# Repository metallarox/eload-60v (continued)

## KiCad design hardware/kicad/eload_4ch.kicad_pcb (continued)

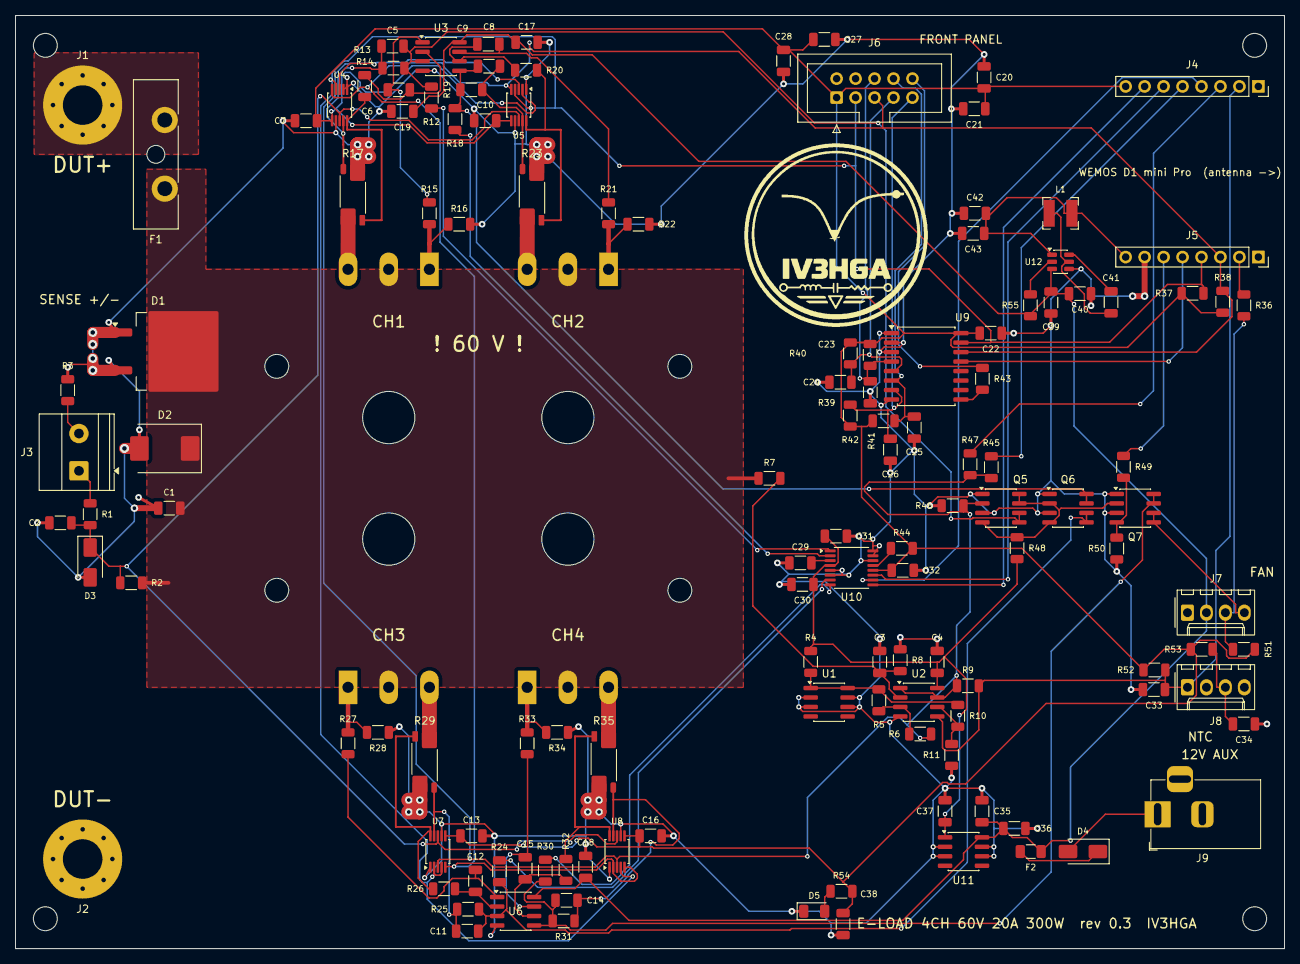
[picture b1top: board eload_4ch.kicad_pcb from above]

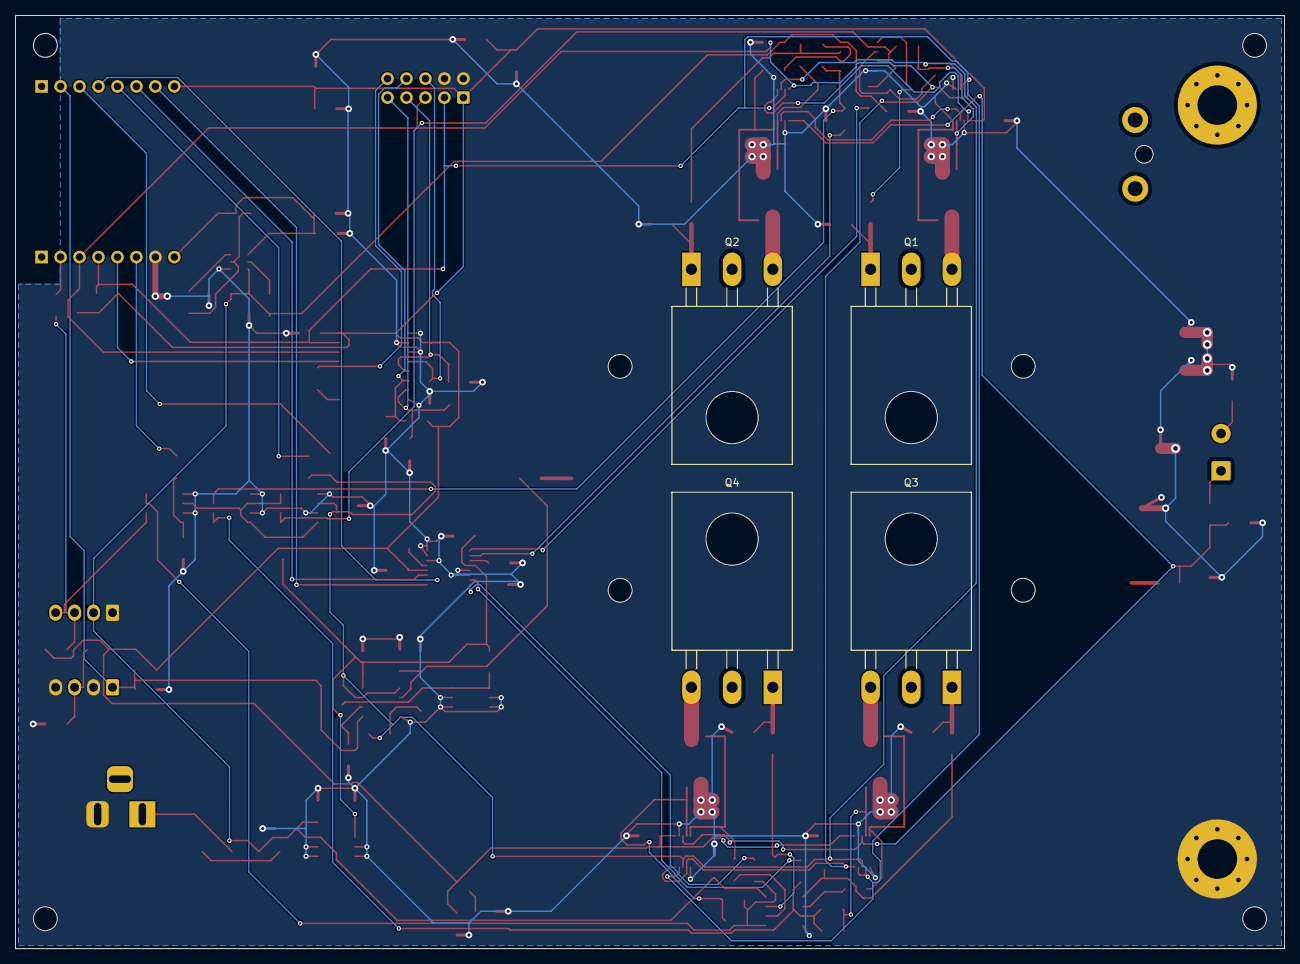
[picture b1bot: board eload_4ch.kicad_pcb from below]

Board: 2 copper layers, 170.0 x 125.0 mm, 143 parts (4 on the bottom side), 77 nets.

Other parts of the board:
H1, H2, H3, H4: M3; MountingHole_3.2mm_M3
H5, H6, H7, H8: M3 nylon (spreader); MountingHole_3.2mm_M3
LOGO1: Logo_IV3HGA; Logo_IV3HGA_25mm

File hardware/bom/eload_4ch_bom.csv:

"Reference","Qty","Value","Footprint","MPN","Note"
"C1","1","100n 100V","Capacitor_SMD:C_1206_3216Metric","","X7R"
"C2","1","10n 100V","Capacitor_SMD:C_1206_3216Metric","",""
"C3,C4,C7,C10,C13,C16,C20,C22,C28-C30,C32-C34,C36","15","100n","Capacitor_SMD:C_1206_3216Metric","",""
"C5,C8,C11,C14","4","10n C0G","Capacitor_SMD:C_1206_3216Metric","","Setpoint filter 16.6 kHz (rev 0.2)"
"C6,C9,C12,C15","4","1n C0G","Capacitor_SMD:C_1206_3216Metric","","Loop compensation rev 0.2: PM ~80 deg, BW 6-15 kHz"
"C17,C18,C40,C41","4","100n 50V","Capacitor_SMD:C_1206_3216Metric","",""
"C19,C21,C27,C35,C38,C39","6","10u 25V","Capacitor_SMD:C_1206_3216Metric","","OLED decoupling"
"C23-C26","4","10n","Capacitor_SMD:C_1206_3216Metric","","Debounce 100 us"
"C31,C37","2","1u","Capacitor_SMD:C_1206_3216Metric","",""
"C42,C43","2","22u 10V","Capacitor_SMD:C_1206_3216Metric","",""
"D1","1","VS-30CTQ100S","Package_TO_SOT_SMD:TO-263-2","VS-30CTQ100SPbF","Reverse polarity: conducts and blows F1 (check I2t)"
"D2","1","SMCJ64CA","Diode_SMD:D_SMC","SMCJ64CA",""
"D3","1","SMAJ64CA","Diode_SMD:D_SMA","SMAJ64CA",""
"D4","1","SS34","Diode_SMD:D_SMA","SS34",""
"D5","1","green","LED_SMD:LED_1206_3216Metric","",""
"F1","1","25A ATO","Fuse:Fuseholder_Blade_ATO_Littelfuse_Pudenz_2_Pin","","ATO blade fuse 25 A"
"F2","1","1.5A","Fuse:Fuse_1206_3216Metric","","PTC 1206, 1.5 A hold (WiFi buck + fan)"
"J1","1","DUT+","MountingHole:MountingHole_5.3mm_M5_Pad_Via","","M5 stud, 25 A"
"J2","1","DUT-","MountingHole:MountingHole_5.3mm_M5_Pad_Via","","M5 stud, 25 A - ground star point"
"J3","1","SENSE","TerminalBlock_Phoenix:TerminalBlock_Phoenix_MKDS-1,5-2_1x02_P5.00mm_Horizontal","","1=SENSE+ 2=SENSE-"
"J4","1","D1mini L","Connector_PinSocket_2.54mm:PinSocket_1x08_P2.54mm_Vertical","","RST A0 D0(GPIO16) D5(14) D6(12) D7(13) D8(15) 3V3; the module 3V3 powers the logic"
"J5","1","D1mini R","Connector_PinSocket_2.54mm:PinSocket_1x08_P2.54mm_Vertical","","TX RX(GPIO3) D1(5) D2(4) D3(0)=expander INT D4(2) G 5V; GPIO0/2/15 = strapping"
"J6","1","FRONT PANEL","Connector_IDC:IDC-Header_2x05_P2.54mm_Vertical","","10-wire ribbon to the front panel: OLED SSD1309/SH1106 0x3C, EC11 encoder, OUTPUT button"
"J7","1","FAN","Connector_Molex:Molex_KK-254_AE-6410-04A_1x04_P2.54mm_Vertical","","12 V 4-wire fan (SP3/TR4 cooler)"
"J8","1","NTC","Connector_Molex:Molex_KK-254_AE-6410-04A_1x04_P2.54mm_Vertical","","2x NTC 10k B3950 glued to the spreader"
"J9","1","12V DC","Connector_BarrelJack:BarrelJack_Horizontal","",""
"L1","1","6u8","Inductor_SMD:L_Bourns-SRN4018","SRN4018-6R8M",""
"Q1-Q4","4","IXTH75N10L2","Package_TO_SOT_THT:TO-247-3_Horizontal_TabUp","IXTH75N10L2","Linear L2 MOSFET 100 V, under the PCB screwed to the spreader (common drain)"
"Q5-Q7","3","FDS9926A","Package_SO:SOIC-8_3.9x4.9mm_P1.27mm","FDS9926A","ARM -> CLAMP inverter"
"Q6,Q7","2","FDS9926A","Package_SO:SOIC-8_3.9x4.9mm_P1.27mm","","Open-drain fan PWM (inverted logic in firmware)"
"R1,R15,R21,R27,R33,R49","6","100R","Resistor_SMD:R_1206_3216Metric","",""
"R2,R5,R8,R16,R22,R28,R34,R39-R42,R44,R46,R48,R51","15","10k","Resistor_SMD:R_1206_3216Metric","","0.1%,Fallback when sense leads are not connected,Pull-down: ARM low = load disabled"
"R3","1","10R","Resistor_SMD:R_1206_3216Metric","","SENSE- referenced to ground only"
"R4,R14,R20,R26,R32,R36,R45","7","1k","Resistor_SMD:R_1206_3216Metric","","Tach on RX: unplug the fan when programming over USB"
"R6,R9","2","1M","Resistor_SMD:R_1206_3216Metric","","OTP hysteresis,OVP hysteresis"
"R7","1","249k","Resistor_SMD:R_1206_3216Metric","","1206 >= 200 V"
"R10,R47,R50,R55","4","100k","Resistor_SMD:R_1206_3216Metric","","ARM read-back: 100k, a GPIO driven at boot cannot arm the load"
"R11","1","9k31","Resistor_SMD:R_1206_3216Metric","","OTP threshold ~100 C"
"R12,R18,R24,R30","4","24k 0.1%","Resistor_SMD:R_1206_3216Metric","","25:1 divider: 2.5 V -> 100 mV = 5 A"
"R13,R19,R25,R31","4","1k 0.1%","Resistor_SMD:R_1206_3216Metric","",""
"R17,R23,R29,R35","4","20m 1%","Resistor_SMD:R_Shunt_Vishay_WSK2512_6332Metric_T1.19mm","WSK2512R0200FEA","4-terminal Kelvin shunt"
"R37,R38","2","2k2","Resistor_SMD:R_1206_3216Metric","","Bus extended to the front panel (rev 0.3)"
"R43","1","470R","Resistor_SMD:R_1206_3216Metric","","OUTPUT LED on the panel: anode to 3V3, cathode here"
"R52,R53","2","10k 0.1%","Resistor_SMD:R_1206_3216Metric","","NTC2 spare: the D1 mini has a single ADC (A0 = NTC1)"
"R54","1","1k5","Resistor_SMD:R_1206_3216Metric","",""
"U1","1","TL431ID","Package_SO:SOIC-8_3.9x4.9mm_P1.27mm","TL431IDR",""
"U2","1","LM393","Package_SO:SOIC-8_3.9x4.9mm_P1.27mm","LM393DR",""
"U3,U6","2","OPA2196","Package_SO:SOIC-8_3.9x4.9mm_P1.27mm","OPA2196IDR",""
"U4,U5,U7,U8","4","INA228","Package_SO:MSOP-10_3x3mm_P0.5mm","INA228AIDGSR","ALERT open-drain on ARM (over-current / over-power)"
"U6","1","OPA2196","Package_SO:SOIC-8_3.9x4.9mm_P1.27mm","OPA2196IDR",""
"U9","1","PCF8574T","Package_SO:SOIC-16W_7.5x10.3mm_P1.27mm","PCF8574T/3","I2C expander @0x20; INT on GPIO0 (D3)"
"U10","1","DAC8565","Package_SO:TSSOP-16_4.4x5mm_P0.65mm","DAC8565IAPW","RSTSEL=0: reset to zero scale; LDAC=0: synchronous update"
"U11","1","L78L05","Package_SO:SOIC-8_3.9x4.9mm_P1.27mm","L78L05ACD13TR",""
"U12","1","AP63205WU","Package_TO_SOT_SMD:TSOT-23-6","AP63205WU-7","FB tied to the 5 V output (fixed-output version)"

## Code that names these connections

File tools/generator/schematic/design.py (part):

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D1.append(('title', 'DUT terminals and power-path protection', 22, 34))
M(d.add(S1, g, 'Connector_Generic:Conn_01x01', 'DUT+', 'MountingHole:MountingHole_5.3mm_M5_Pad_Via', {1: 'DUT_P'}, 'J',
        note='M5 stud, 25 A'), 30.48, 50.8, 180, wired=[1])
M(d.add(S1, g, 'Device:Fuse', '25A ATO', 'Fuse:Fuseholder_Blade_ATO_Littelfuse_Pudenz_2_Pin', {1: 'DUT_P', 2: 'VLOAD'}, 'F',
        note='ATO blade fuse 25 A'), 48.26, 50.8, 90, wired=[1, 2])
D1.append(('wire', [(35.56, 50.8), (44.45, 50.8)]))
D1.append(('wire', [(52.07, 50.8), (63.5, 50.8), (86.36, 50.8), (106.68, 50.8), (124.46, 50.8)]))
D1.append(('label', 'VLOAD', 124.46, 50.8, (1, 0)))
for xx in (63.5, 86.36, 106.68):
    D1.append(('junc', xx, 50.8))
    D1.append(('wire', [(xx, 50.8), (xx, 54.61)]))
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M(r(S1, g, '100R', 'SENSE_P_EXT', 'VSENSE'), 45.72, 111.76, 90, wired=[1, 2])
D1.append(('wire', [(35.56, 111.76), (41.91, 111.76)]))
D1.append(('wire', [(49.53, 111.76), (58.42, 111.76), (68.58, 111.76), (78.74, 111.76), (91.44, 111.76)]))
D1.append(('label', 'VSENSE', 91.44, 111.76, (1, 0)))
for xx in (58.42, 68.58):
    D1.append(('junc', xx, 111.76))
    D1.append(('wire', [(xx, 111.76), (xx, 115.57)]))
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D1.append(('wire', [(33.02, 167.64), (30.48, 167.64), (30.48, 162.56), (35.56, 162.56)]))
D1.append(('junc', 35.56, 162.56))
D1.append(('wire', [(35.56, 162.56), (45.72, 162.56), (73.66, 162.56)]))
D1.append(('label', 'VREF_2V5', 45.72, 162.56, (0, -1)))
# OVP
M(r(S1, g, '10k', 'VREF_2V5', 'OVP_REF'), 73.66, 170.18, wired=[1, 2])
D1.append(('wire', [(73.66, 162.56), (73.66, 166.37)]))
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         91.44, 180.34, wired=[1, 2, 3])
D1.append(('wire', [(99.06, 180.34), (101.6, 180.34), (109.22, 180.34)]))
D1.append(('junc', 101.6, 180.34))
D1.append(('label', 'ARM', 109.22, 180.34, (1, 0)))
M(r(S1, g, '249k', 'VLOAD', 'OVP_DIV', note='1206 >= 200 V'), 60.96, 187.96, wired=[2])
M(r(S1, g, '10k', 'OVP_DIV', 'GND', note='0.1%'), 60.96, 200.66, wired=[1])
M(c(S1, g, '100n', 'OVP_DIV', 'GND'), 71.12, 200.66, wired=[1])
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D1.append(('junc', 71.12, 194.31))
D1.append(('wire', [(78.74, 194.31), (78.74, 182.88), (83.82, 182.88)]))
# OTP
D1.append(('label', 'NTC1', 147.32, 177.8, (-1, 0)))
D1.append(('wire', [(147.32, 177.8), (160.02, 177.8), (167.64, 177.8)]))
D1.append(('junc', 160.02, 177.8))
D1.append(('wire', [(160.02, 177.8), (160.02, 167.64), (168.91, 167.64)]))
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  175.26, 180.34, wired=[5, 6, 7])
D1.append(('wire', [(182.88, 180.34), (185.42, 180.34), (193.04, 180.34)]))
D1.append(('junc', 185.42, 180.34))
D1.append(('label', 'ARM', 193.04, 180.34, (1, 0)))
M(r(S1, g, '100k', 'VREF_2V5', 'OTP_REF'), 152.4, 187.96, 90, wired=[1, 2])
D1.append(('wire', [(148.59, 187.96), (146.05, 187.96)]))
D1.append(('label', 'VREF_2V5', 146.05, 187.96, (-1, 0)))
D1.append(('wire', [(156.21, 187.96), (162.56, 187.96), (165.1, 187.96), (165.1, 182.88), (167.64, 182.88)]))
D1.append(('junc', 162.56, 187.96))
M(r(S1, g, '9k31', 'OTP_REF', 'GND', note='OTP threshold ~100 C'), 162.56, 195.58, wired=[1])
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g = 'ARM'
D3 = d.draw[S3] = []
D3.append(('title', 'ARM / CLAMP logic  (fail-safe: load off if the MCU is missing, in reset or faulty)', 22, 34))
D3.append(('label', 'ARM_DRV', 25.4, 63.5, (-1, 0)))
D3.append(('wire', [(25.4, 63.5), (27.94, 63.5)]))
M(r(S3, g, '1k', 'ARM_DRV', 'ARM'), 31.75, 63.5, 90, wired=[1, 2])
D3.append(('wire', [(35.56, 63.5), (43.18, 63.5), (50.8, 63.5), (58.42, 63.5), (81.28, 63.5)]))
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D3.append(('wire', [(43.18, 63.5), (43.18, 67.31)]))
D3.append(('wire', [(58.42, 63.5), (58.42, 67.31)]))
D3.append(('wire', [(50.8, 63.5), (50.8, 55.88)]))
D3.append(('label', 'ARM', 50.8, 55.88, (0, -1)))
M(r(S3, g, '10k', 'ARM', 'GND', note='Pull-down: ARM low = load disabled'), 43.18, 71.12, wired=[1])
M(r(S3, g, '100k', 'ARM', 'ARM_FB', note='ARM read-back: 100k, a GPIO driven at boot cannot arm the load'), 58.42, 71.12, wired=[1])
qa = M(d.add(S3, g, 'Transistor_FET:FDS9926A', 'FDS9926A', SOIC8, {2: 'ARM', 7: 'CLAMP', 8: 'CLAMP', 1: 'GND'}, 'Q', unit=1,
             mpn='FDS9926A', note='ARM -> CLAMP inverter'), 86.36, 63.5, wired=[2, 7, 8])
D3.append(('wire', [(88.9, 58.42), (88.9, 50.8), (96.52, 50.8), (104.14, 50.8)]))
D3.append(('junc', 96.52, 50.8))
D3.append(('label', 'CLAMP', 104.14, 50.8, (1, 0)))
M(r(S3, g, '10k', '+5V', 'CLAMP'), 96.52, 44.45, wired=[2])
D3.append(('wire', [(96.52, 48.26), (96.52, 50.8)]))
M(d.add(S3, g, 'Transistor_FET:FDS9926A', 'FDS9926A', SOIC8, {4: 'CLAMP', 5: 'VSET1', 6: 'VSET1', 3: 'GND'}, 'Q', unit=2, ref=qa.ref),
  132.08, 63.5)
qb = M(d.add(S3, g, 'Transistor_FET:FDS9926A', 'FDS9926A', SOIC8, {2: 'CLAMP', 7: 'VSET2', 8: 'VSET2', 1: 'GND'}, 'Q', unit=1,
             mpn='FDS9926A'), 157.48, 63.5)
M(d.add(S3, g, 'Transistor_FET:FDS9926A', 'FDS9926A', SOIC8, {4: 'CLAMP', 5: 'VSET3', 6: 'VSET3', 3: 'GND'}, 'Q', unit=2, ref=qb.ref),
  182.88, 63.5)
qc = M(d.add(S3, g, 'Transistor_FET:FDS9926A', 'FDS9926A', SOIC8, {2: 'CLAMP', 7: 'VSET4', 8: 'VSET4', 1: 'GND'}, 'Q', unit=1,
             mpn='FDS9926A'), 208.28, 63.5)
D3.append(('text', 'CLAMP high -> setpoints VSET1..4 shorted to ground', 124.46, 80))

g = '4-wire PWM fan and NTC sensors on the spreader'
d.add(S3, g, 'Transistor_FET:FDS9926A', 'FDS9926A', SOIC8, {4: 'FAN_PWM_G', 5: 'FAN_PWM', 6: 'FAN_PWM', 3: 'GND'}, 'Q', unit=2,
      ref=qc.ref, note='Open-drain fan PWM (inverted logic in firmware)')
r(S3, g, '100R', 'FAN_PWM_MCU', 'FAN_PWM_G')
r(S3, g, '100k', 'FAN_PWM_G', 'GND')
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    'ARM (active high, 10k pull-down) enables the load. LM393 (OVP 64.7 V, OTP ~100 C) and the INA228 ALERTs pull it low in hardware.',
    'ARM low -> CLAMP high -> clamp FETs short VSET1..4 to ground. MCU in reset = load off.',
    'Single GND = DUT- (star point at stud J2). Control over WiFi only; the Wemos USB is NOT isolated: use it only for programming with the DUT disconnected.',
    'ESP8266 firmware: after SPI.begin() re-assign GPIO12 as output (ARM_DRV); GPIO16 = ARM_FB; A0 = NTC1 (D1 mini internal 220k/100k divider).',
    'Front panel (rev 0.3): PCF8574 @0x20 (encoder A/B/SW, OUTPUT button, LED), INT on GPIO0; OLED @0x3C on the same bus. OUTPUT ON enables ARM, never automatic.',
    '#Exceptions to the SMD SOIC/SOP + 1206 passives rule',
    'TO-247 power MOSFETs (mounted on the spreader), WSK2512 Kelvin shunts, D2PAK reverse-polarity diode, SMC/SMA TVS,',
    'INA228 in VSSOP-10 (0.5 mm pitch), DAC8565 in TSSOP-16, AP63205 in TSOT-23-6, SRN4018 inductor, THT connectors.',
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
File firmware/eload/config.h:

// eload-60v firmware - hardware configuration (rev 0.3 board, Wemos LOLIN D1 mini Pro)
#pragma once
#include <stdint.h>

#define FW_VERSION "0.2.0"
#define FW_NAME    "eload-60v"

// ---------------------------------------------------------------- pins (ESP8266 GPIO numbers)
#define PIN_I2C_SDA   4     // D2
#define PIN_I2C_SCL   5     // D1
// SPI uses the ESP8266 HSPI pins: SCK = GPIO14 (D5), MOSI = GPIO13 (D7)
#define PIN_DAC_SYNC  15    // D8, DAC8565 SYNC (low at boot thanks to the module pull-down)
#define PIN_ARM_DRV   12    // D6, drives ARM through 1k. HIGH = load armed. Re-assign after SPI.begin()!
#define PIN_ARM_FB    16    // D0, reads ARM through 100k (hardware trip detection)
#define PIN_FAN_PWM   2     // D4, gate of the open-drain fan PWM FET (inverted)
#define PIN_FAN_TACH  3     // RX, fan tach (Serial runs TX-only)
#define PIN_EXP_INT   0     // D3, PCF8574 INT (front panel)
#define PIN_NTC       A0    // NTC1 through the D1 mini 220k/100k divider

// ---------------------------------------------------------------- I2C addresses
static const uint8_t INA_ADDR[4] = {0x40, 0x41, 0x42, 0x43};
#define PCF8574_ADDR  0x20
#define OLED_ADDR     0x3C

// ---------------------------------------------------------------- analog front end
#define R_SHUNT       0.020f      // ohm, per channel
#define DIVIDER       25.0f       // DAC -> setpoint divider (24k / 1k)
#define DAC_VREF      2.5f        // DAC8565 internal reference
#define DAC_FS        65535.0f
// I = Vdac / (DIVIDER * R_SHUNT) -> 2 A/V, 5 A at 2.5 V

// ---------------------------------------------------------------- ratings and limits
#define N_CH          4
#define I_CH_MAX      5.0f        // A per channel
#define P_CH_MAX      75.0f       // W per channel (MOSFET SOA / thermal budget)
#define V_MAX         60.0f       // V, rated input
#define I_KEEPALIVE   0.010f      // A per channel while the output is on (fast response from idle)
#define T_SPREADER_MAX 85.0f      // C, firmware over-temperature (hardware OTP trips at ~100 C)

// INA228 hardware limits -> ALERT -> ARM (latched)
#define INA_OVP_V     63.0f       // bus over-voltage
#define INA_OCP_A     5.25f       // per channel over-current
#define INA_OPP_W     80.0f       // per channel over-power

// ---------------------------------------------------------------- fan / NTC
#define NTC_R25       10000.0f
#define NTC_BETA      3950.0f
#define NTC_PULLUP    10000.0f
#define NTC_VCC       3.3f
#define A0_DIVIDER    3.2f        // D1 mini: 220k / 100k in front of the 1 V ADC
#define A0_LOAD       320000.0f   // the same divider loads the NTC node
#define FAN_T_LOW     35.0f       // C -> minimum fan speed
#define FAN_T_HIGH    65.0f       // C -> full speed
#define FAN_MIN_DUTY  0.25f

// ---------------------------------------------------------------- pulsed (modulated) load
// The sink alternates between the setpoint (high phase) and the keep-alive current (low phase).
// The CC loop needs ~30-50 us per edge (10-90 %), so each phase lasts at least PULSE_T_MIN_US.
#define PULSE_F_MIN     0.1f      // Hz
#define PULSE_F_MAX     1000.0f   // Hz
#define PULSE_D_MIN     1.0f      // % duty (time at the setpoint)
#define PULSE_D_MAX     99.0f     // %
#define PULSE_T_MIN_US  100.0f    // us, shortest high or low phase

// ---------------------------------------------------------------- timing
#define CONTROL_PERIOD_MS  50
#define DISPLAY_PERIOD_MS  200
#define HISTORY_LEN        600     // RAM history samples (1 s each -> 10 min)
